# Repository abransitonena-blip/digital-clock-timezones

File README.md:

# AP · Iluminación LED inteligente

Sitio web (React + Vite) y diseños abiertos de electrónica para iluminación LED.

## Secciones del sitio
| Ruta | Qué hace |
|---|---|
| `#` Inicio | Presentación del Cubo AP, líneas de producto y proyectos |
| `#lineas` | 7 líneas de producto con configuración recomendada y ejemplo calculado. Líneas: letreros, arquitectura, hogar, comercio, eventos, solar y vehículos |
| `#cubo` | Ficha del Cubo AP y **panel de control**: Bluetooth (Chrome/Edge) o demo simulada |
| `#configurador` | Pedidos por cliente (V, A, cantidad), con exportación a CSV e impresión. Calcula: cubos, cartucho, tarjeta con R_B/R_ID, cable, lista de compra y **cotización** (tus costos, margen e IVA) |
| `#calculadora` | Consumo, reinyección, cubos y caída en cable para 15 tiras del mercado. Incluye la tarjeta a la medida (R_B E96) |
| `#compatibilidad` | Compatibilidad con tiras, apps, asistentes de voz y fuentes de energía |
| `#instalar` | Graba el firmware del Cubo AP por USB desde Chrome o Edge (ESP Web Tools empaquetado, sin CDN) |
| `#proyectos` | Todos los proyectos de `hardware/`, con manuales, esquemas, Gerber y BOM |
| `#reloj` | El reloj mundial original (zonas horarias, alarmas, temas) |

```
npm install
npm run dev      # http://localhost:3000
npm test         # pruebas de los cálculos (src/lib/led.test.js)
npm run build    # sitio estático en dist/ (rutas relativas: sirve en GitHub Pages o cualquier hosting)
```
- `src/lib/led.js` tiene los cálculos, sin React. Sus perfiles de tarjeta son los mismos del firmware.
- `src/datos/catalogo.js` tiene las tiras, las líneas de producto, la compatibilidad y los proyectos.
- `public/cubo-app.html` es el panel ligero; se copia al compilar desde `hardware/cubo-led-modular/app/index.html`, y es la misma página que el cubo sirve por Wi-Fi.

## Publicar
- **GitHub Pages:** `.github/workflows/pages.yml` compila, prueba y publica en cada push a `main`. Hay que activarlo una vez en *Settings → Pages → Source: GitHub Actions*.
- **Sin internet:** el sitio se puede instalar en el celular o la PC como app (PWA). Después de la primera visita funciona sin red; esto requiere HTTPS o localhost.

Los diseños están sin fabricar ni certificar. Los consumos de tiras son típicos: confírmalos con la ficha del fabricante.

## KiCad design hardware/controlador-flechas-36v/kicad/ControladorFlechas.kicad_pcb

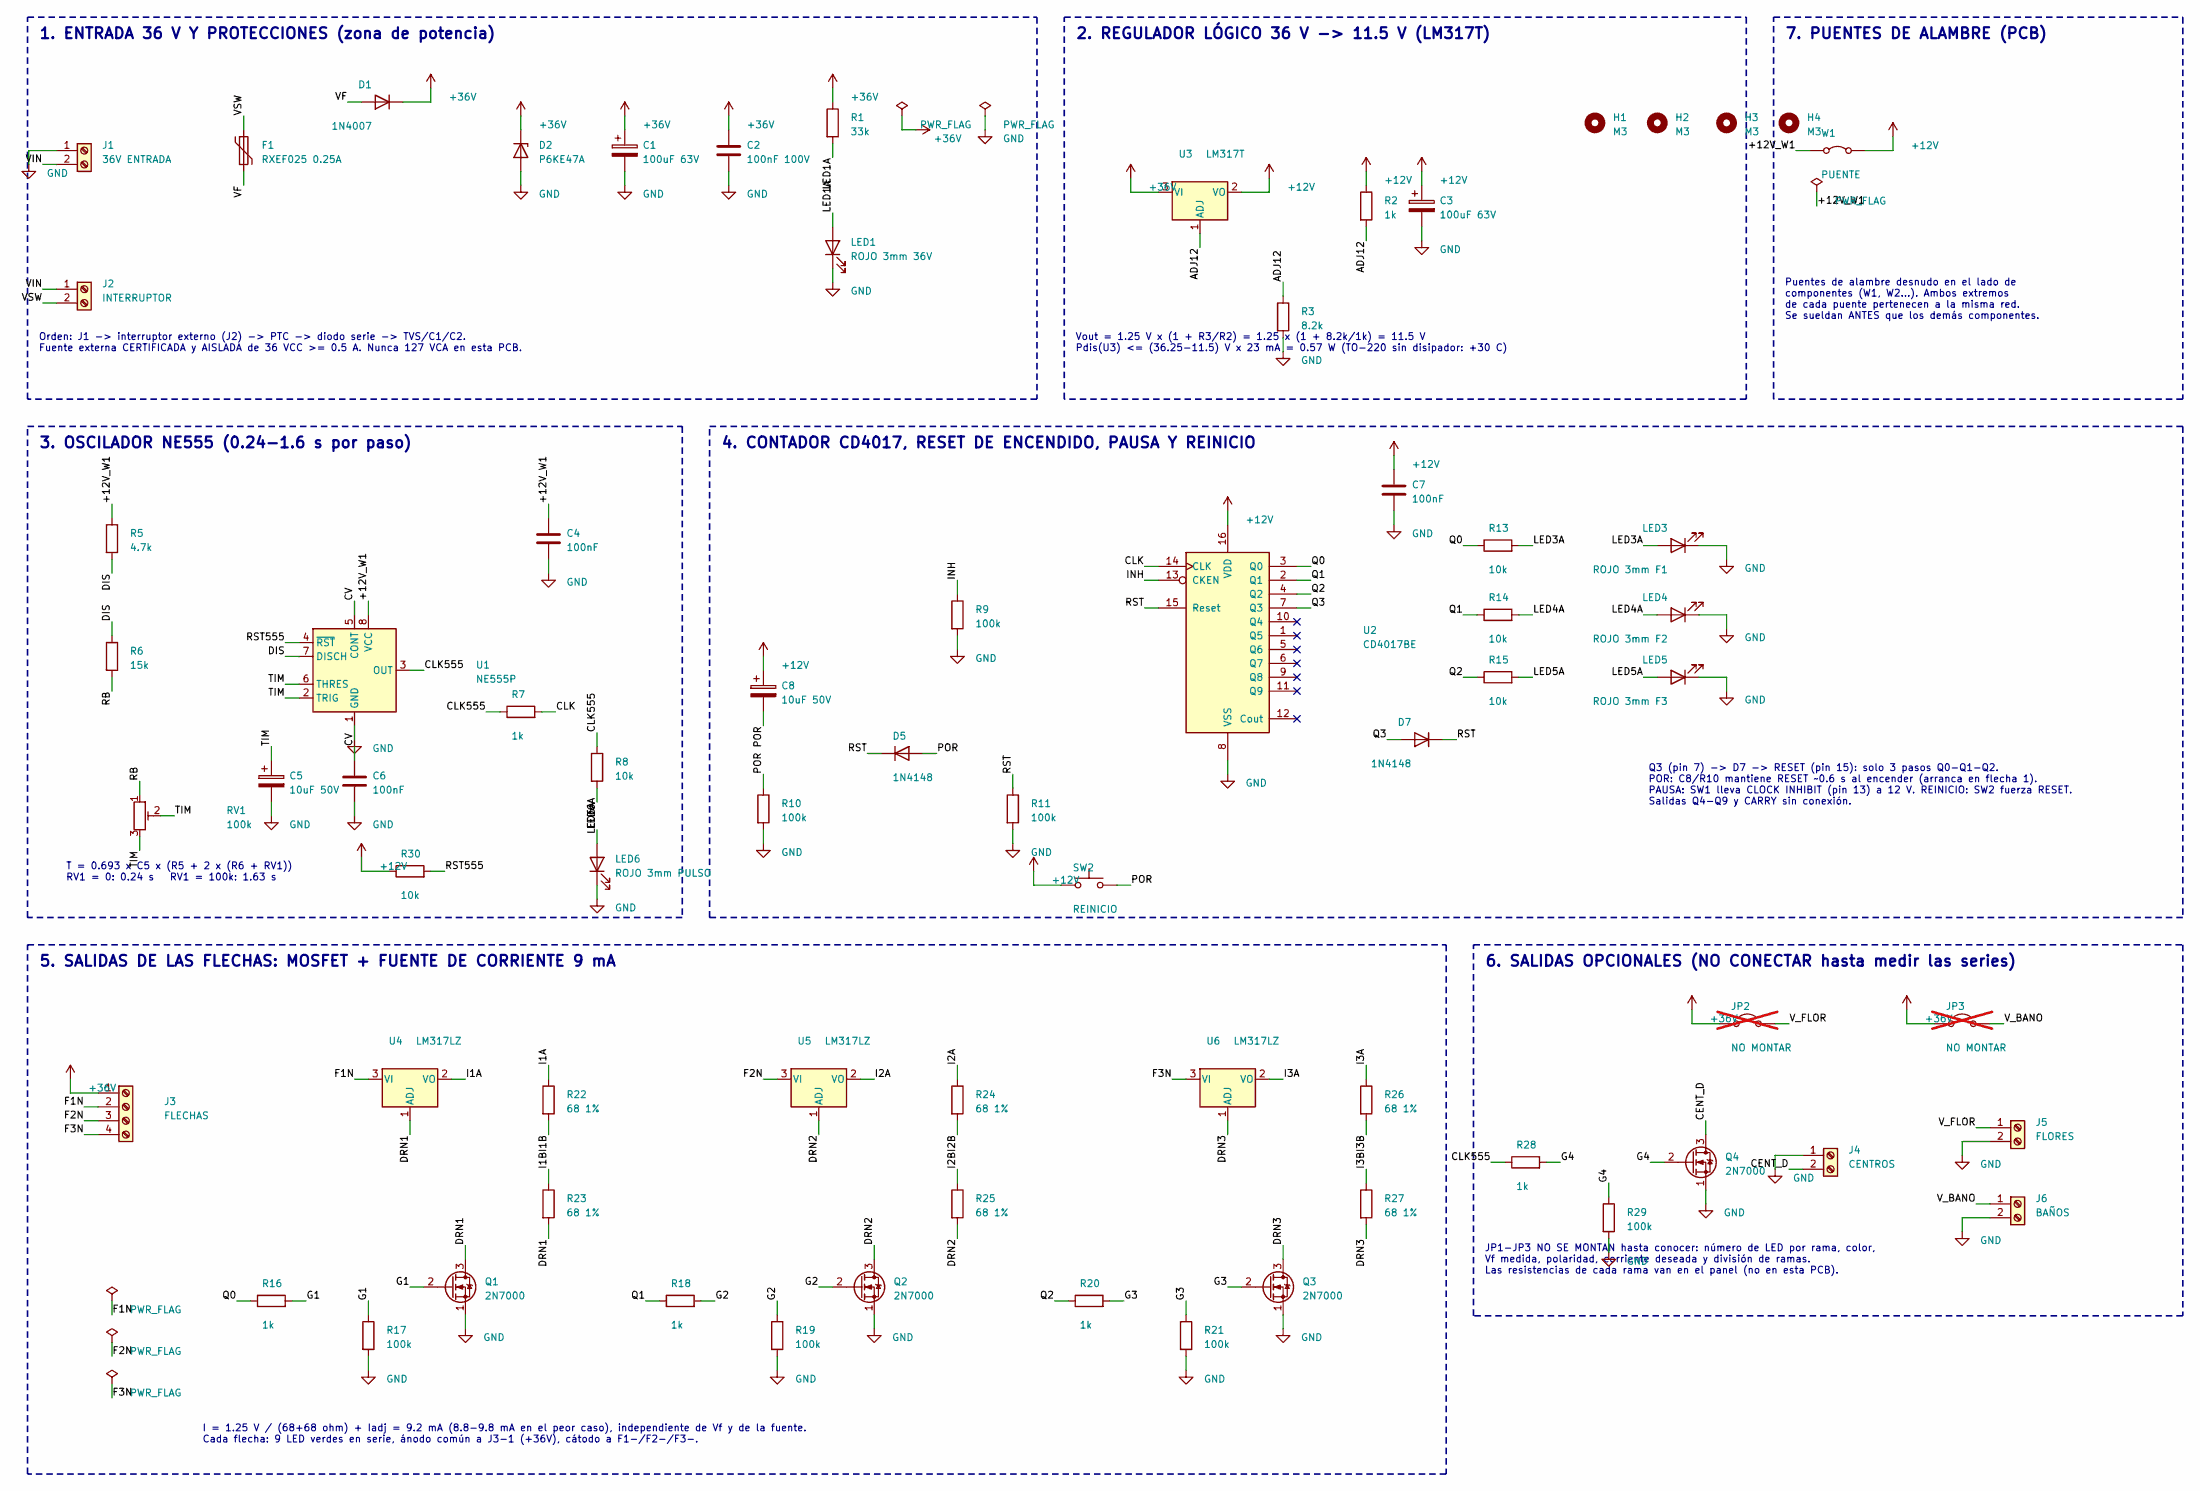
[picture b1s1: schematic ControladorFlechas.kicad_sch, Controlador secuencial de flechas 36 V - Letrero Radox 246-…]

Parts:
C1, C3: 100uF 63V; CP_Radial_D8.0mm_P3.81mm
C2: 100nF 100V; C_Disc_P5.08mm
C4, C6, C7: 100nF; C_Disc_P5.08mm
C5, C8: 10uF 50V; CP_Radial_D5.0mm_P2.54mm
D1: 1N4007; D_DO-41_P10.16mm
D2: P6KE47A; D_DO-15_P12.70mm
D5, D7: 1N4148; D_DO-35_P7.62mm
F1: RXEF025 0.25A; PTC_Radial_P5.08mm
H1, H2, H3, H4: M3; Barreno_M3_3.2mm
J1: 36V ENTRADA; Clema_2P_P5.08mm
J2: INTERRUPTOR; Clema_2P_P5.08mm
J3: FLECHAS; Clema_4P_P5.08mm
J4: CENTROS; Clema_2P_P5.08mm
J5: FLORES; Clema_2P_P5.08mm
J6: BAÑOS; Clema_2P_P5.08mm
JP2, JP3: NO MONTAR; Enlace_Opcional_P7.62mm; not fitted
LED1: ROJO 3mm 36V; LED_D3.0mm
LED3: ROJO 3mm F1; LED_D3.0mm
LED4: ROJO 3mm F2; LED_D3.0mm
LED5: ROJO 3mm F3; LED_D3.0mm
LED6: ROJO 3mm PULSO; LED_D3.0mm
Q1, Q2, Q3, Q4: 2N7000; TO-92_2N7000
R1: 33k; R_Vertical_P5.08mm
R2, R28: 1k; R_Vertical_P5.08mm
R3: 8.2k; R_Vertical_P5.08mm
R5: 4.7k; R_Vertical_P5.08mm
R6: 15k; R_Vertical_P5.08mm
R7, R16, R18, R20: 1k; R_Axial_P10.16mm
R8, R13, R14, R15: 10k; R_Vertical_P5.08mm
R9: 100k; R_Axial_P10.16mm
R10, R11, R17, R19, R21, R29: 100k; R_Vertical_P5.08mm
R22, R23, R24, R25, R26, R27: 68 1%; R_Vertical_P5.08mm
R30: 10k; R_Axial_P10.16mm
RV1: 100k; Trimpot_3296W
SW2: REINICIO; Boton_6mm
U1: NE555P; DIP-8_W7.62mm
U2: CD4017BE; DIP-16_W7.62mm
U3: LM317T; TO-220-3_Vertical
U4, U5, U6: LM317LZ; TO-92_LM317L
W1: PUENTE; Puente_Alambre_P7.62mm

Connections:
+12V: C3.1, C7.1, C8.1, R2.1, R30.1, SW2.1, U2.16 (VDD), U3.2 (VO), W1.2 (B)
+36V: C1.1, C2.1, D1.1 (K), D2.1 (K), J3.1, JP2.1 (A), JP3.1 (A), R1.1, U3.3 (VI)
/+12V_W1: C4.1, R5.1, U1.8 (VCC), W1.1 (A)
/ADJ12: R2.2, R3.1, U3.1 (ADJ)
/CENT_D: J4.2, Q4.3 (D)
/CLK: R7.2, U2.14 (CLK)
/CLK555: R7.1, R8.1, R28.1, U1.3 (OUT)
/CV: C6.1, U1.5 (CONT)
/DIS: R5.2, R6.1, U1.7 (DISCH)
/DRN1: Q1.3 (D), R23.2, U4.1 (ADJ)
/DRN2: Q2.3 (D), R25.2, U5.1 (ADJ)
/DRN3: Q3.3 (D), R27.2, U6.1 (ADJ)
/F1N: J3.2, U4.3 (VI)
/F2N: J3.3, U5.3 (VI)
/F3N: J3.4, U6.3 (VI)
/G1: Q1.2 (G), R16.2, R17.1
/G2: Q2.2 (G), R18.2, R19.1
/G3: Q3.2 (G), R20.2, R21.1
/G4: Q4.2 (G), R28.2, R29.1
/I1A: R22.1, U4.2 (VO)
/I1B: R22.2, R23.1
/I2A: R24.1, U5.2 (VO)
/I2B: R24.2, R25.1
/I3A: R26.1, U6.2 (VO)
/I3B: R26.2, R27.1
/INH: R9.1, U2.13 (CKEN)
/LED1A: LED1.2 (A), R1.2
/LED3A: LED3.2 (A), R13.2
/LED4A: LED4.2 (A), R14.2
/LED5A: LED5.2 (A), R15.2
/LED6A: LED6.2 (A), R8.2
/POR: C8.2, D5.2 (A), R10.1, SW2.2
/Q0: R13.1, R16.1, U2.3 (Q0)
/Q1: R14.1, R18.1, U2.2 (Q1)
/Q2: R15.1, R20.1, U2.4 (Q2)
/Q3: D7.2 (A), U2.7 (Q3)
/RB: R6.2, RV1.1
/RST: D5.1 (K), D7.1 (K), R11.1, U2.15 (Reset)
/RST555: R30.2, U1.4 (~RST)
/TIM: C5.1, RV1.2, RV1.3, U1.2 (TRIG), U1.6 (THRES)
/VF: D1.2 (A), F1.2
/VIN: J1.2, J2.1
/VSW: F1.1, J2.2
/V_BANO: J6.1, JP3.2 (B)
/V_FLOR: J5.1, JP2.2 (B)
GND: C1.2, C2.2, C3.2, C4.2, C5.2, C6.2, C7.2, D2.2 (A), J1.1, J4.1, J5.2, J6.2, LED1.1 (K), LED3.1 (K), LED4.1 (K), LED5.1 (K), LED6.1 (K), Q1.1 (S), Q2.1 (S), Q3.1 (S), Q4.1 (S), R3.2, R9.2, R10.2, R11.2, R17.2, R19.2, R21.2, R29.2, U1.1 (GND), U2.8 (VSS)

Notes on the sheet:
1. ENTRADA 36 V Y PROTECCIONES (zona de potencia)
2. REGULADOR LÓGICO 36 V -> 11.5 V (LM317T)
3. OSCILADOR NE555 (0.24-1.6 s por paso)
4. CONTADOR CD4017, RESET DE ENCENDIDO, PAUSA Y REINICIO
5. SALIDAS DE LAS FLECHAS: MOSFET + FUENTE DE CORRIENTE 9 mA
6. SALIDAS OPCIONALES (NO CONECTAR hasta medir las series)
7. PUENTES DE ALAMBRE (PCB)
Orden: J1 -> interruptor externo (J2) -> PTC -> diodo serie -> TVS/C1/C2. Fuente externa CERTIFICADA y AISLADA de 36 VCC >= 0.5 A. Nunca 127 VCA en esta PCB.
Vout = 1.25 V x (1 + R3/R2) = 1.25 x (1 + 8.2k/1k) = 11.5 V Pdis(U3) <= (36.25-11.5) V x 23 mA = 0.57 W (TO-220 sin disipador: +30 C)
T = 0.693 x C5 x (R5 + 2 x (R6 + RV1)) RV1 = 0: 0.24 s RV1 = 100k: 1.63 s
Q3 (pin 7) -> D7 -> RESET (pin 15): solo 3 pasos Q0-Q1-Q2. POR: C8/R10 mantiene RESET ~0.6 s al encender (arranca en flecha 1). PAUSA: SW1 lleva CLOCK INHIBIT (pin 13) a 12 V. REINICIO: SW2 fuerza RESET. Salidas Q4-Q9 y CARRY sin conexión.
I = 1.25 V / (68+68 ohm) + Iadj = 9.2 mA (8.8-9.8 mA en el peor caso), independiente de Vf y de la fuente. Cada flecha: 9 LED verdes en serie, ánodo común a J3-1 (+36V), cátodo a F1-/F2-/F3-.
Puentes de alambre desnudo en el lado de componentes (W1, W2...). Ambos extremos de cada puente pertenecen a la misma red. Se sueldan ANTES que los demás componentes.
JP1-JP3 NO SE MONTAN hasta conocer: número de LED por rama, color, Vf medida, polaridad, corriente deseada y división de ramas. Las resistencias de cada rama van en el panel (no en esta PCB).

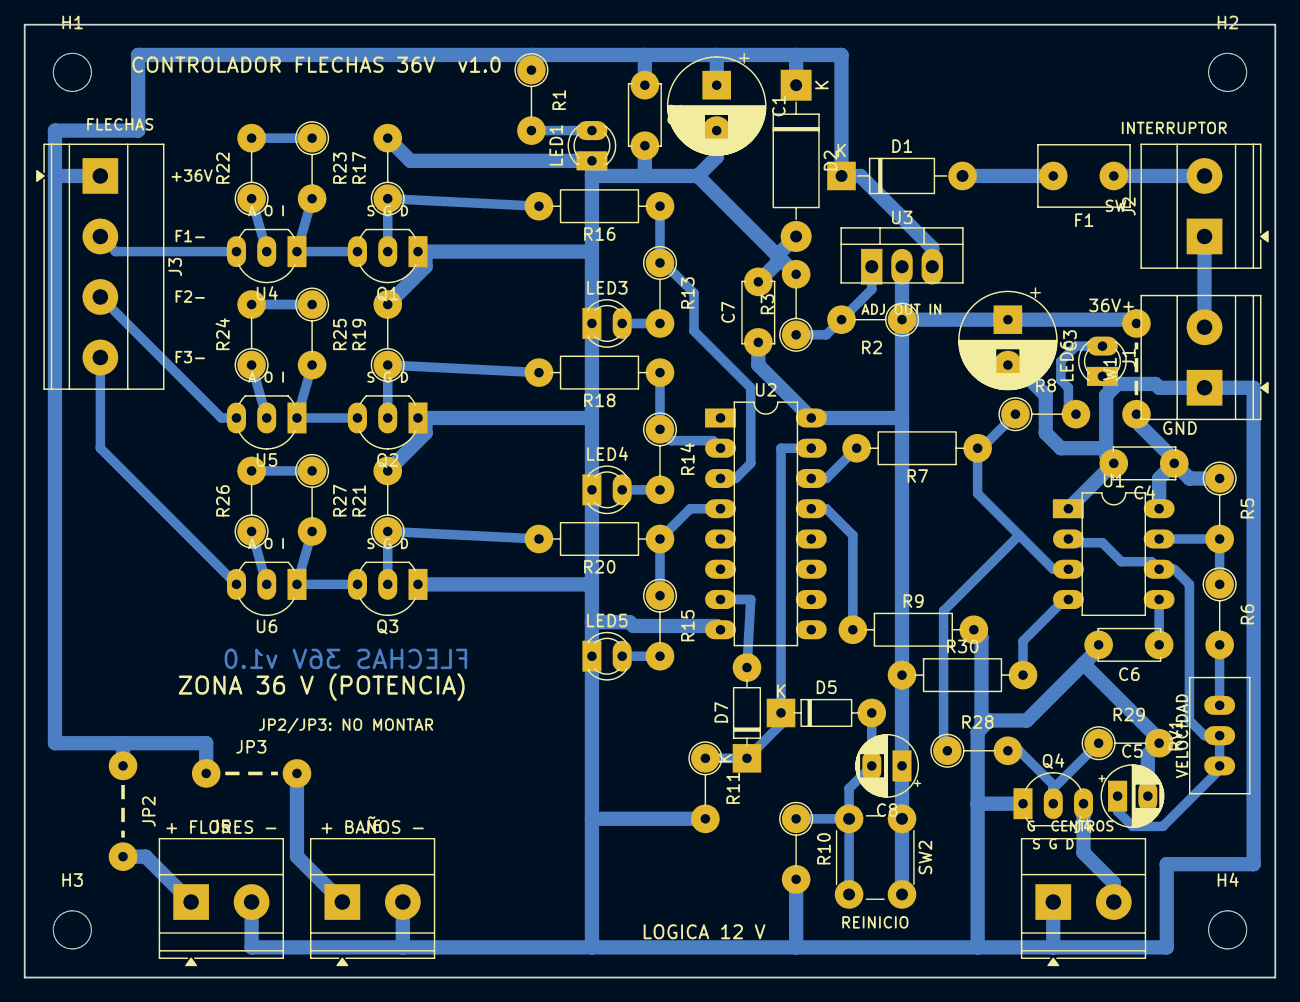
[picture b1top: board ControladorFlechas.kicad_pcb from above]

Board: 2 copper layers, 105.0 x 80.0 mm, 71 parts (0 on the bottom side), 46 nets.

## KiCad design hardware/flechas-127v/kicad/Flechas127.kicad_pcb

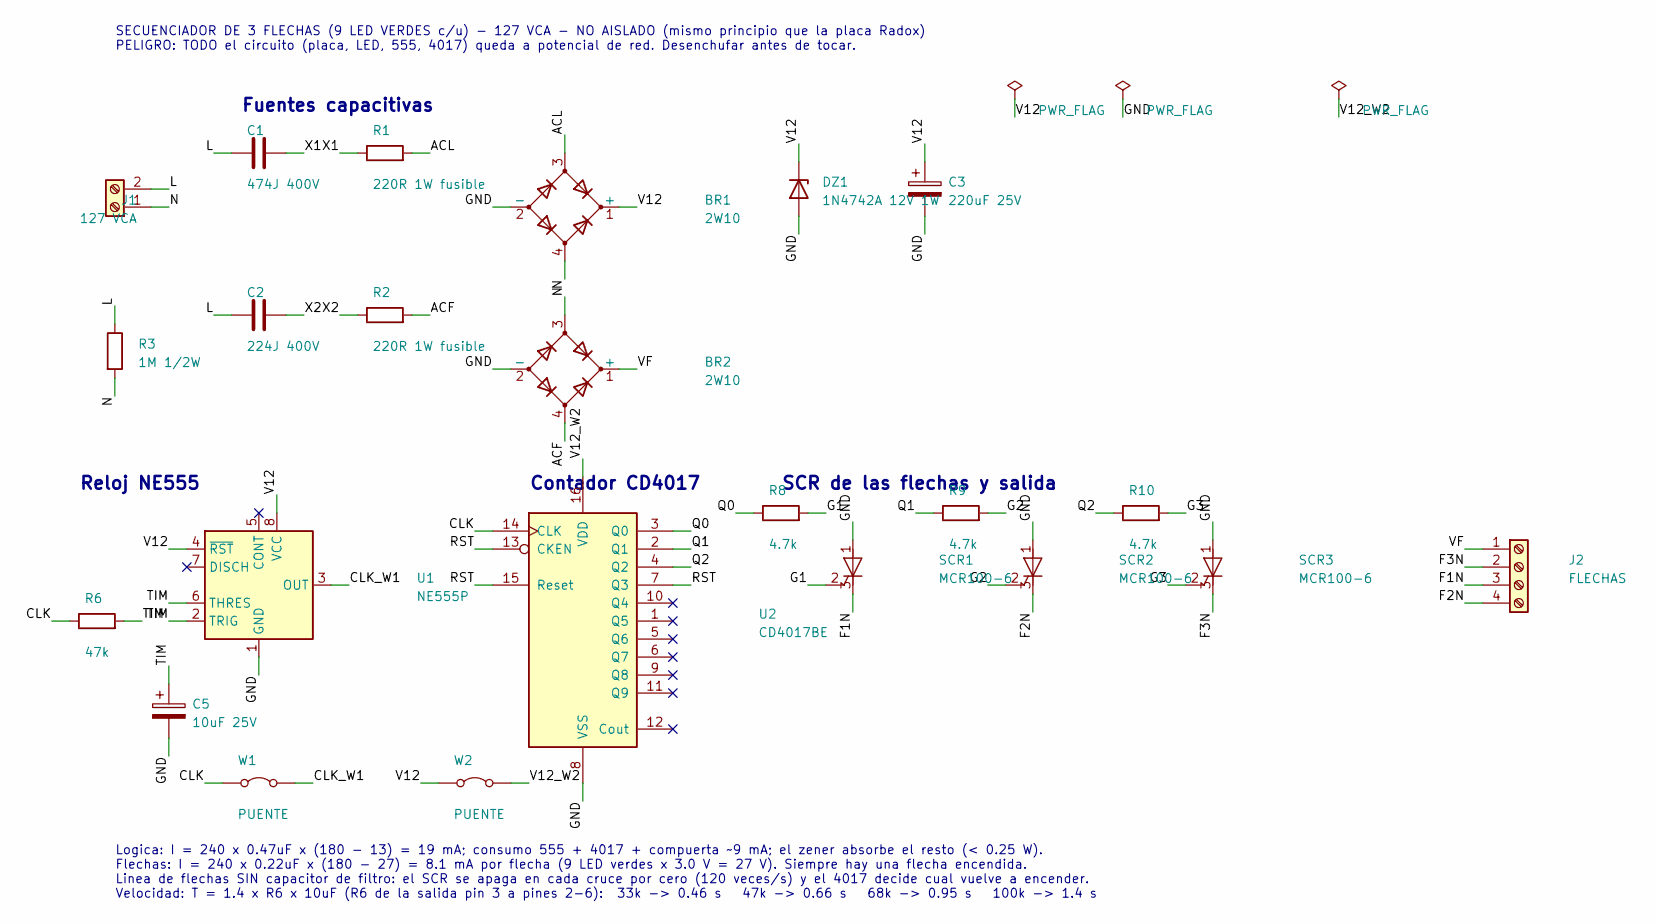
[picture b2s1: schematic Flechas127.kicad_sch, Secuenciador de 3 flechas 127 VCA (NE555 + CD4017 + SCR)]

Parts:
BR1, BR2: 2W10; Puente_2W10
C1: 474J 400V; C_Poliester_P10-15mm
C2: 224J 400V; C_Poliester_P10-15mm
C3: 220uF 25V; CP_Radial_D8.0mm_P3.81mm
C5: 10uF 25V; CP_Radial_D5.0mm_P2.54mm
DZ1: 1N4742A 12V 1W; D_DO-41_P10.16mm
J1: 127 VCA; Clema_2P_P5.08mm
J2: FLECHAS; Cables_4P_P5.08mm
R1, R2: 220R 1W fusible; R_1W_Vertical_P7.62mm
R3: 1M 1/2W; R_Vertical_P5.08mm
R6: 47k; R_Vertical_P5.08mm
R8, R9, R10: 4.7k; R_Vertical_P5.08mm
SCR1, SCR2, SCR3: MCR100-6; TO-92_SCR
U1: NE555P; DIP-8_W7.62mm
U2: CD4017BE; DIP-16_W7.62mm
W1: PUENTE; Puente_Abajo_P7.62mm
W2: PUENTE; Puente_Abajo_P10.16mm

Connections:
/ACF: BR2.4, R2.2
/ACL: BR1.3, R1.2
/CLK: R6.1, U2.14 (CLK), W1.1 (A)
/CLK_W1: U1.3 (OUT), W1.2 (B)
/F1N: J2.3, SCR1.3 (K)
/F2N: J2.4, SCR2.3 (K)
/F3N: J2.2, SCR3.3 (K)
/G1: R8.2, SCR1.2 (G)
/G2: R9.2, SCR2.2 (G)
/G3: R10.2, SCR3.2 (G)
/GND: BR1.2 (-), BR2.2 (-), C3.2, C5.2, DZ1.2 (A), SCR1.1 (A), SCR2.1 (A), SCR3.1 (A), U1.1 (GND), U2.8 (VSS)
/L: C1.1, C2.1, J1.2, R3.1
/N: BR1.4, BR2.3, J1.1, R3.2
/Q0: R8.1, U2.3 (Q0)
/Q1: R9.1, U2.2 (Q1)
/Q2: R10.1, U2.4 (Q2)
/RST: U2.7 (Q3), U2.13 (CKEN), U2.15 (Reset)
/TIM: C5.1, R6.2, U1.2 (TRIG), U1.6 (THRES)
/V12: BR1.1 (+), C3.1, DZ1.1 (K), U1.4 (~RST), U1.8 (VCC), W2.1 (A)
/V12_W2: U2.16 (VDD), W2.2 (B)
/VF: BR2.1 (+), J2.1
/X1: C1.2, R1.1
/X2: C2.2, R2.1

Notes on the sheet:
SECUENCIADOR DE 3 FLECHAS (9 LED VERDES c/u) - 127 VCA - NO AISLADO (mismo principio que la placa Radox) PELIGRO: TODO el circuito (placa, LED, 555, 4017) queda a potencial de red. Desenchufar antes de tocar.
Logica: I = 240 x 0.47uF x (180 - 13) = 19 mA; consumo 555 + 4017 + compuerta ~9 mA; el zener absorbe el resto (< 0.25 W). Flechas: I = 240 x 0.22uF x (180 - 27) = 8.1 mA por flecha (9 LED verdes x 3.0 V = 27 V). Siempre hay una flecha encendida. Linea de flechas SIN capacitor de filtro: el SCR se 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
Fuentes capacitivas
Reloj NE555
Contador CD4017
SCR de las flechas y salida

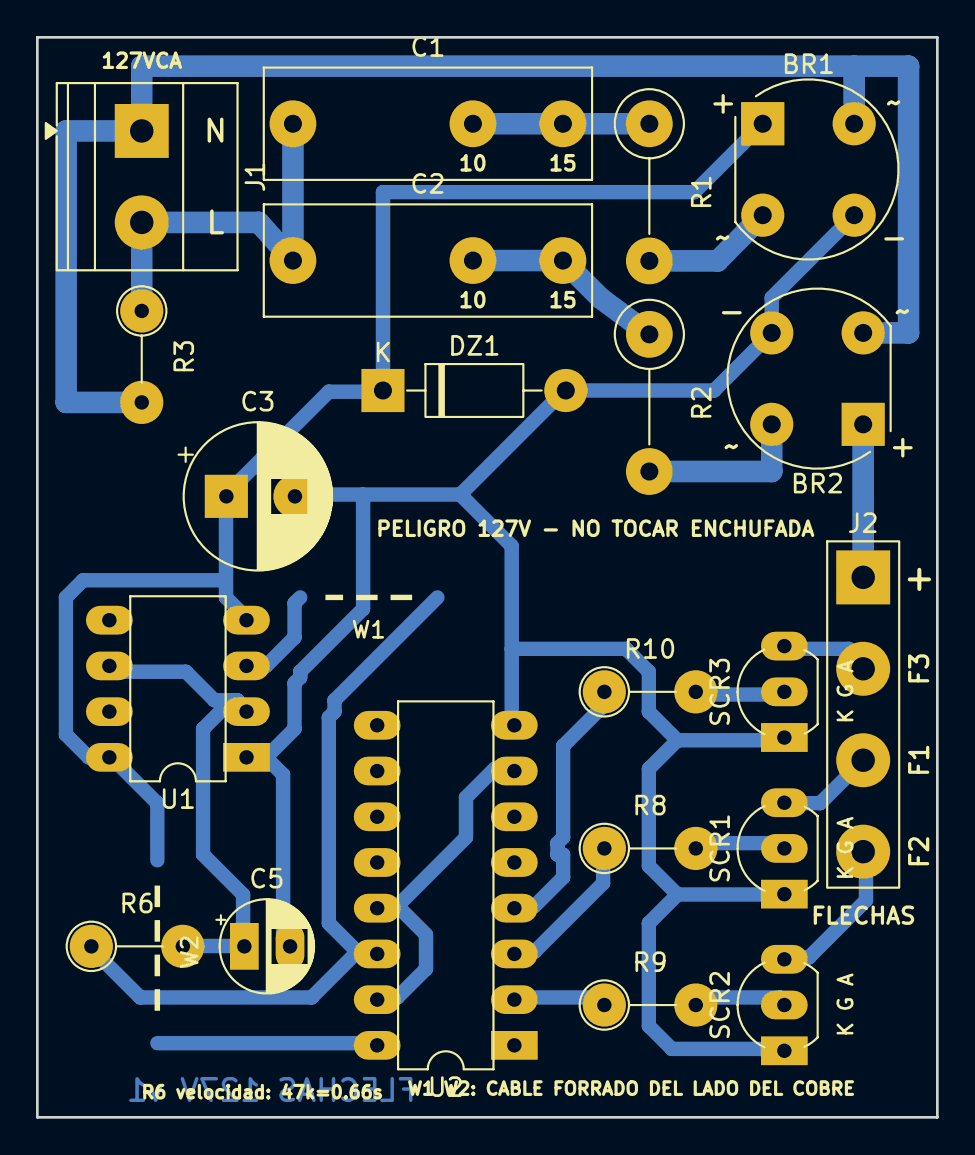
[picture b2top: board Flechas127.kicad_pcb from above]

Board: 2 copper layers, 50.0 x 60.0 mm, 23 parts (0 on the bottom side), 23 nets.

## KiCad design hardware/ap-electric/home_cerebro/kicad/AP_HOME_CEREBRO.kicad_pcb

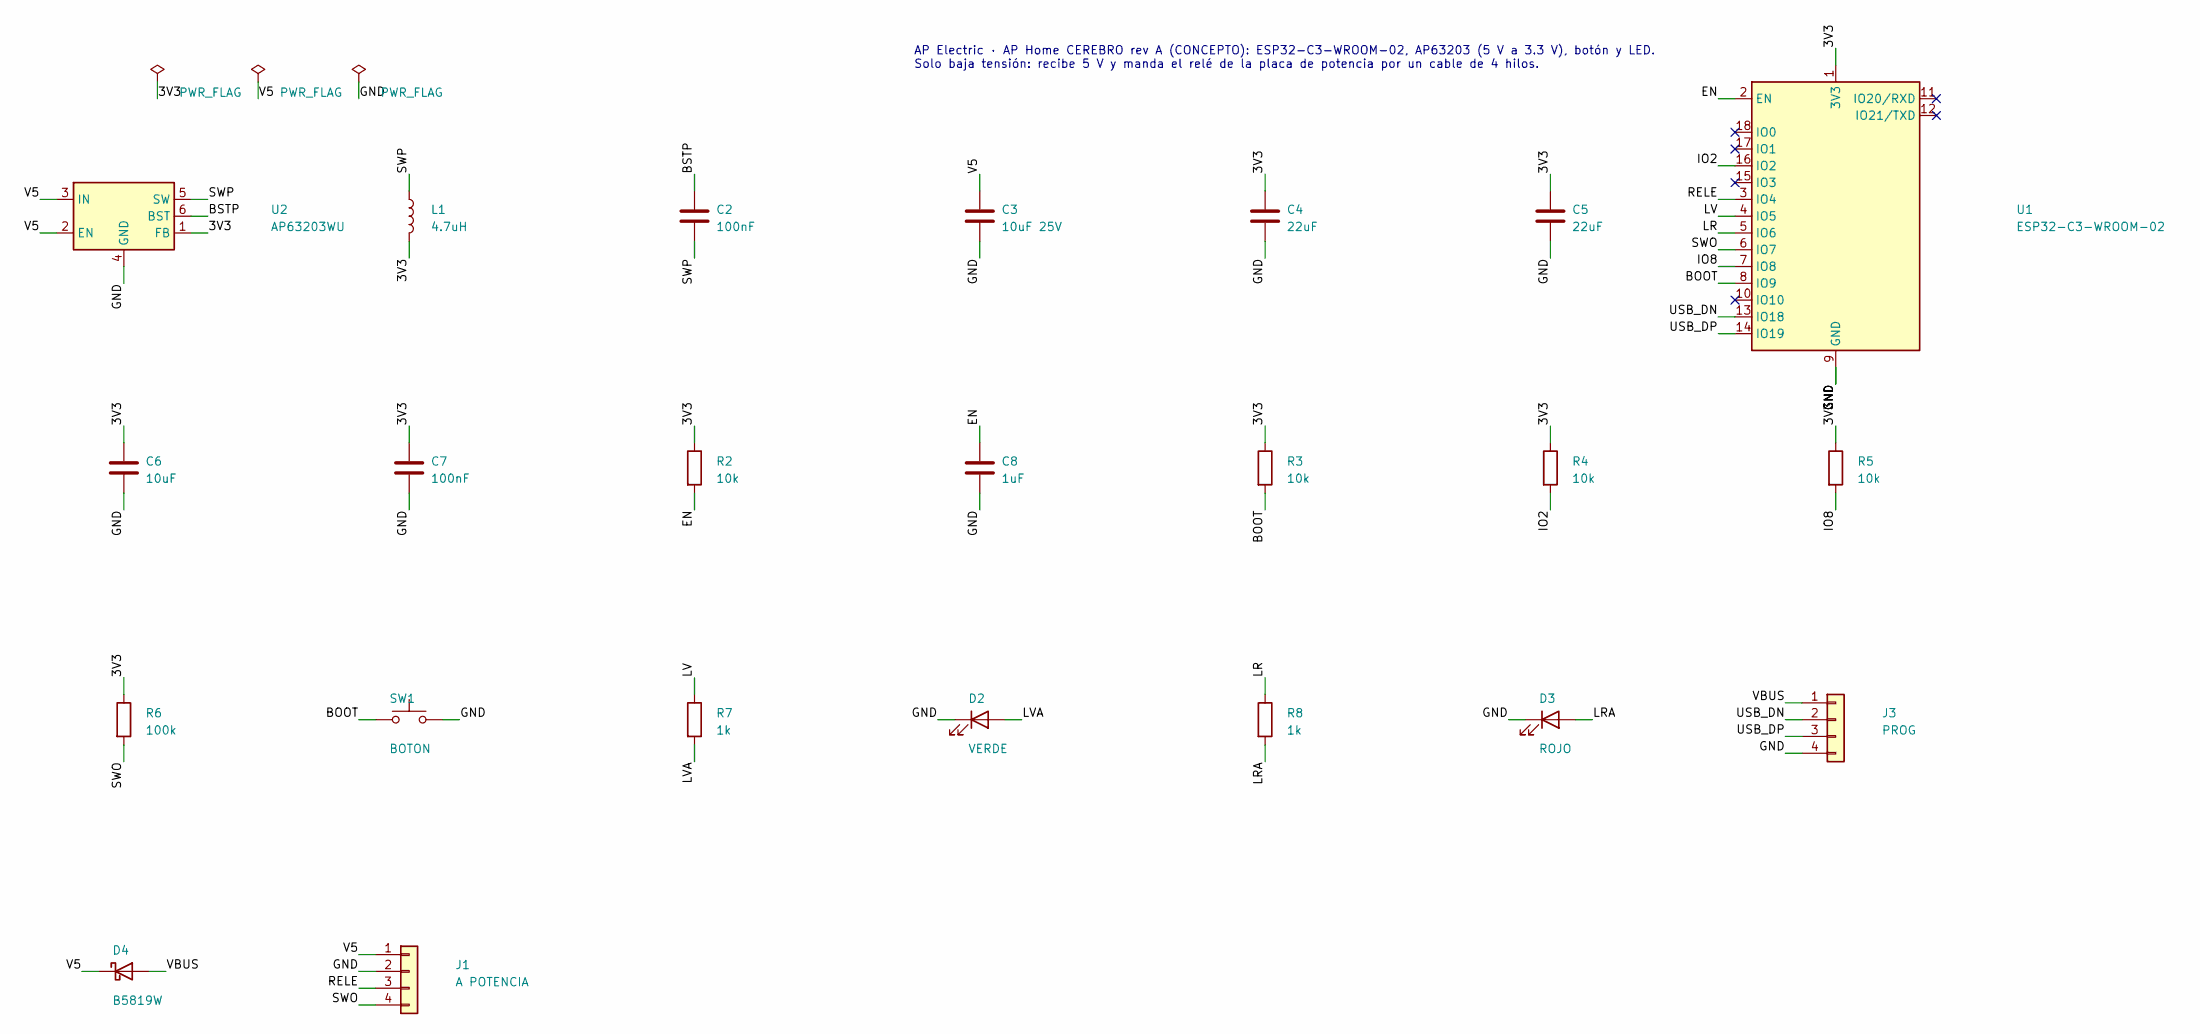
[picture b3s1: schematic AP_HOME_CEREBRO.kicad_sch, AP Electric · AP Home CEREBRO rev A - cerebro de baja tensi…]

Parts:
C2, C7: 100nF; C_0603_1608Metric
C3: 10uF 25V; C_1206_3216Metric
C4, C5: 22uF; C_0805_2012Metric
C6: 10uF; C_0805_2012Metric
C8: 1uF; C_0603_1608Metric
D2: VERDE; LED_0603_1608Metric
D3: ROJO; LED_0603_1608Metric
D4: B5819W; D_SOD-123
J1: A POTENCIA; JST_XH_B4B-XH-A_1x04_P2.50mm_Vertical
J3: PROG; PinHeader_1x04_P2.54mm_Vertical
L1: 4.7uH; L_Changjiang_FNR4030S
R2, R3, R4, R5: 10k; R_0603_1608Metric
R6: 100k; R_0603_1608Metric
R7, R8: 1k; R_0603_1608Metric
SW1: BOTON; SW_Push_1P1T_XKB_TS-1187A
U1: ESP32-C3-WROOM-02; ESP32-C3-WROOM-02_JLC
U2: AP63203WU; TSOT-23-6

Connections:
/3V3: C4.1, C5.1, C6.1, C7.1, L1.2, R2.1, R3.1, R4.1, R5.1, R6.1, U1.1 (3V3), U2.1 (FB)
/BOOT: R3.2, SW1.1, U1.8 (IO9)
/BSTP: C2.1, U2.6 (BST)
/EN: C8.1, R2.2, U1.2 (EN)
/GND: C3.2, C4.2, C5.2, C6.2, C7.2, C8.2, D2.1 (K), D3.1 (K), J1.2, J3.4, SW1.2, U1.9 (GND), U1.19 (GND), U2.4 (GND)
/IO2: R4.2, U1.16 (IO2)
/IO8: R5.2, U1.7 (IO8)
/LR: R8.1, U1.5 (IO6)
/LRA: D3.2 (A), R8.2
/LV: R7.1, U1.4 (IO5)
/LVA: D2.2 (A), R7.2
/RELE: J1.3, U1.3 (IO4)
/SWO: J1.4, R6.2, U1.6 (IO7)
/SWP: C2.2, L1.1, U2.5 (SW)
/USB_DN: J3.2, U1.13 (IO18)
/USB_DP: J3.3, U1.14 (IO19)
/V5: C3.1, D4.1 (K), J1.1, U2.2 (EN), U2.3 (IN)
/VBUS: D4.2 (A), J3.1

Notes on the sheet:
AP Electric · AP Home CEREBRO rev A (CONCEPTO): ESP32-C3-WROOM-02, AP63203 (5 V a 3.3 V), botón y LED. Solo baja tensión: recibe 5 V y manda el relé de la placa de potencia por un cable de 4 hilos.

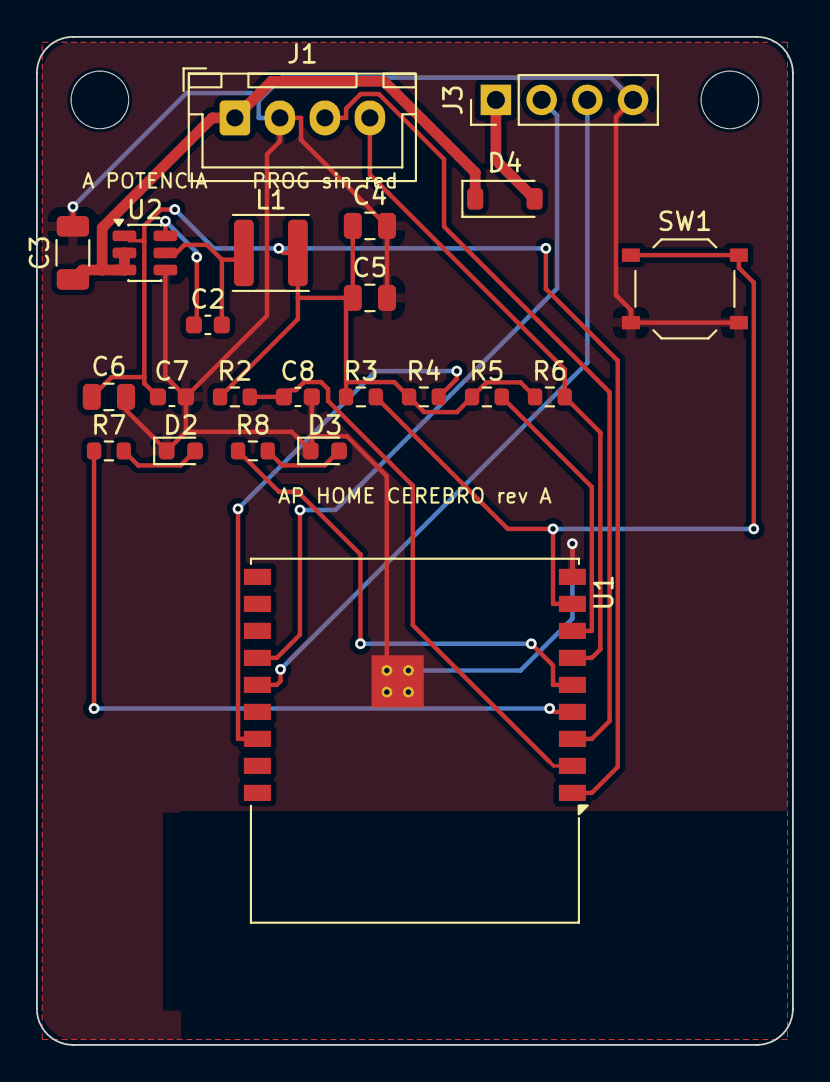
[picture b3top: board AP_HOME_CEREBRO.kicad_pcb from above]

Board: 2 copper layers, 42.0 x 56.0 mm, 25 parts (0 on the bottom side), 18 nets.

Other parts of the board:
H1, H2: MountingHole_3.2mm_M3

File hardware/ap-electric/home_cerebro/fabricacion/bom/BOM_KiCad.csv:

"Referencia","Valor","Huella","Cantidad","Funcion"
"C2,C7","100nF","Capacitor_SMD:C_0603_1608Metric","2","Bootstrap,Desacoplo del módulo"
"C3","10uF 25V","Capacitor_SMD:C_1206_3216Metric","1","Entrada del buck"
"C4,C5","22uF","Capacitor_SMD:C_0805_2012Metric","2","Salida 3.3 V"
"C6","10uF","Capacitor_SMD:C_0805_2012Metric","1","Desacoplo del módulo"
"C8","1uF","Capacitor_SMD:C_0603_1608Metric","1","Arranque retardado"
"D2","VERDE","LED_SMD:LED_0603_1608Metric","1","Encendido"
"D3","ROJO","LED_SMD:LED_0603_1608Metric","1","Falla"
"D4","B5819W","Diode_SMD:D_SOD-123","1","5 V del USB al programar"
"J1","A POTENCIA","Connector_JST:JST_XH_B4B-XH-A_1x04_P2.50mm_Vertical","1","Cable de BAJA tensión a la placa de potencia (JST XH, 1 a 1): 1 = 5 V, 2 = 0 V, 3 = mando del relé (3.3 V), 4 = estado del apagador"
"J3","PROG","Connector_PinHeader_2.54mm:PinHeader_1x04_P2.54mm_Vertical","1","Programación por USB en fábrica, SIN red conectada"
"L1","4.7uH","Inductor_SMD:L_Changjiang_FNR4030S","1","Bobina 3.3 V"
"R2,R3,R4,R5","10k","Resistor_SMD:R_0603_1608Metric","4","IO2 en alto al arrancar,IO8 en alto al arrancar,Pull-up EN,Pull-up IO9"
"R6","100k","Resistor_SMD:R_0603_1608Metric","1","Pull-up de la entrada de apagador"
"R7,R8","1k","Resistor_SMD:R_0603_1608Metric","2","LED rojo,LED verde"
"SW1","BOTON","Button_Switch_SMD:SW_Push_1P1T_XKB_TS-1187A","1","Botón: corto = encender/apagar; 3 s = red de configuración; 10 s = fábrica"
"U1","ESP32-C3-WROOM-02","LetreroLab:ESP32-C3-WROOM-02_JLC","1","IO4 = relé, IO5/IO6 = LED, IO7 = entrada de apagador, IO9 = botón"
"U2","AP63203WU","Package_TO_SOT_SMD:TSOT-23-6","1","Buck 3.3 V"

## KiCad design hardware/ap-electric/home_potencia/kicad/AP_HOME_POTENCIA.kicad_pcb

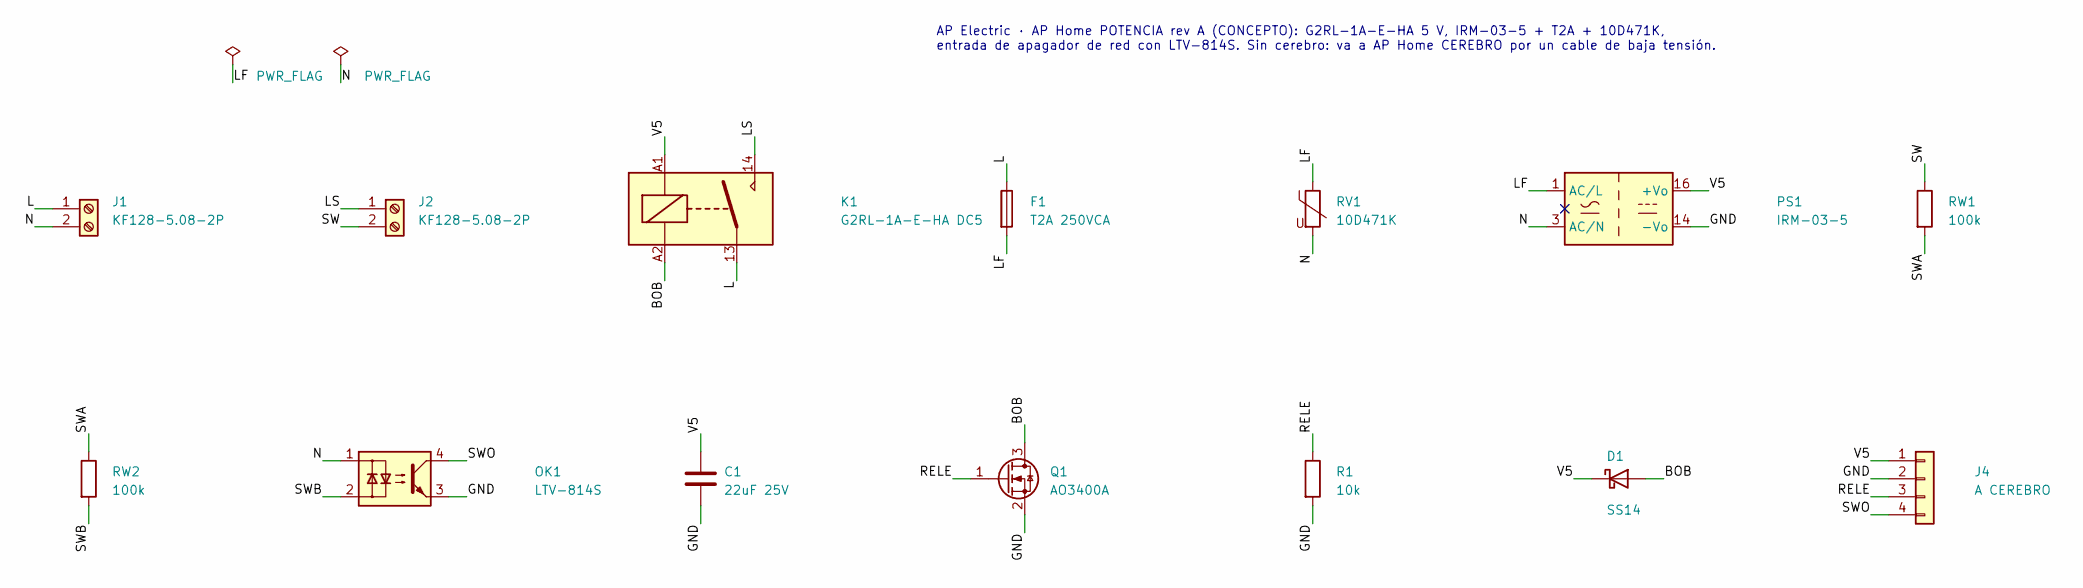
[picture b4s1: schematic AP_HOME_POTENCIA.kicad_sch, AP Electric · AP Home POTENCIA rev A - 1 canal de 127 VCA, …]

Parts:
C1: 22uF 25V; C_1206_3216Metric
D1: SS14; D_SMA
F1: T2A 250VCA; Fuse_2410_6125Metric
J1, J2: KF128-5.08-2P; TerminalBlock_Phoenix_MKDS-1,5-2-5.08_1x02_P5.08mm_Horizont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
J4: A CEREBRO; JST_XH_B4B-XH-A_1x04_P2.50mm_Vertical
K1: G2RL-1A-E-HA DC5; Relay_SPST_Omron_G2RL-1A-E
OK1: LTV-814S; SMDIP-4_W9.53mm
PS1: IRM-03-5; Converter_ACDC_MeanWell_IRM-03-xx_THT
Q1: AO3400A; SOT-23
R1: 10k; R_0603_1608Metric
RV1: 10D471K; RV_Disc_D12mm_W5mm_P7.5mm
RW1, RW2: 100k; R_1206_3216Metric

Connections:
/BOB: D1.2 (A), K1.A2, Q1.3 (D)
/GND: C1.2, J4.2, OK1.3, PS1.14 (-Vo), Q1.2 (S), R1.2
/L: F1.1, J1.1, K1.13
/LF: F1.2, PS1.1 (AC/L), RV1.1
/LS: J2.1, K1.14
/N: J1.2, OK1.1, PS1.3 (AC/N), RV1.2
/RELE: J4.3, Q1.1 (G), R1.1
/SW: J2.2, RW1.1
/SWA: RW1.2, RW2.1
/SWB: OK1.2, RW2.2
/SWO: J4.4, OK1.4
/V5: C1.1, D1.1 (K), J4.1, K1.A1, PS1.16 (+Vo)

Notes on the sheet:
AP Electric · AP Home POTENCIA rev A (CONCEPTO): G2RL-1A-E-HA 5 V, IRM-03-5 + T2A + 10D471K, entrada de apagador de red con LTV-814S. Sin cerebro: va a AP Home CEREBRO por un cable de baja tensión.

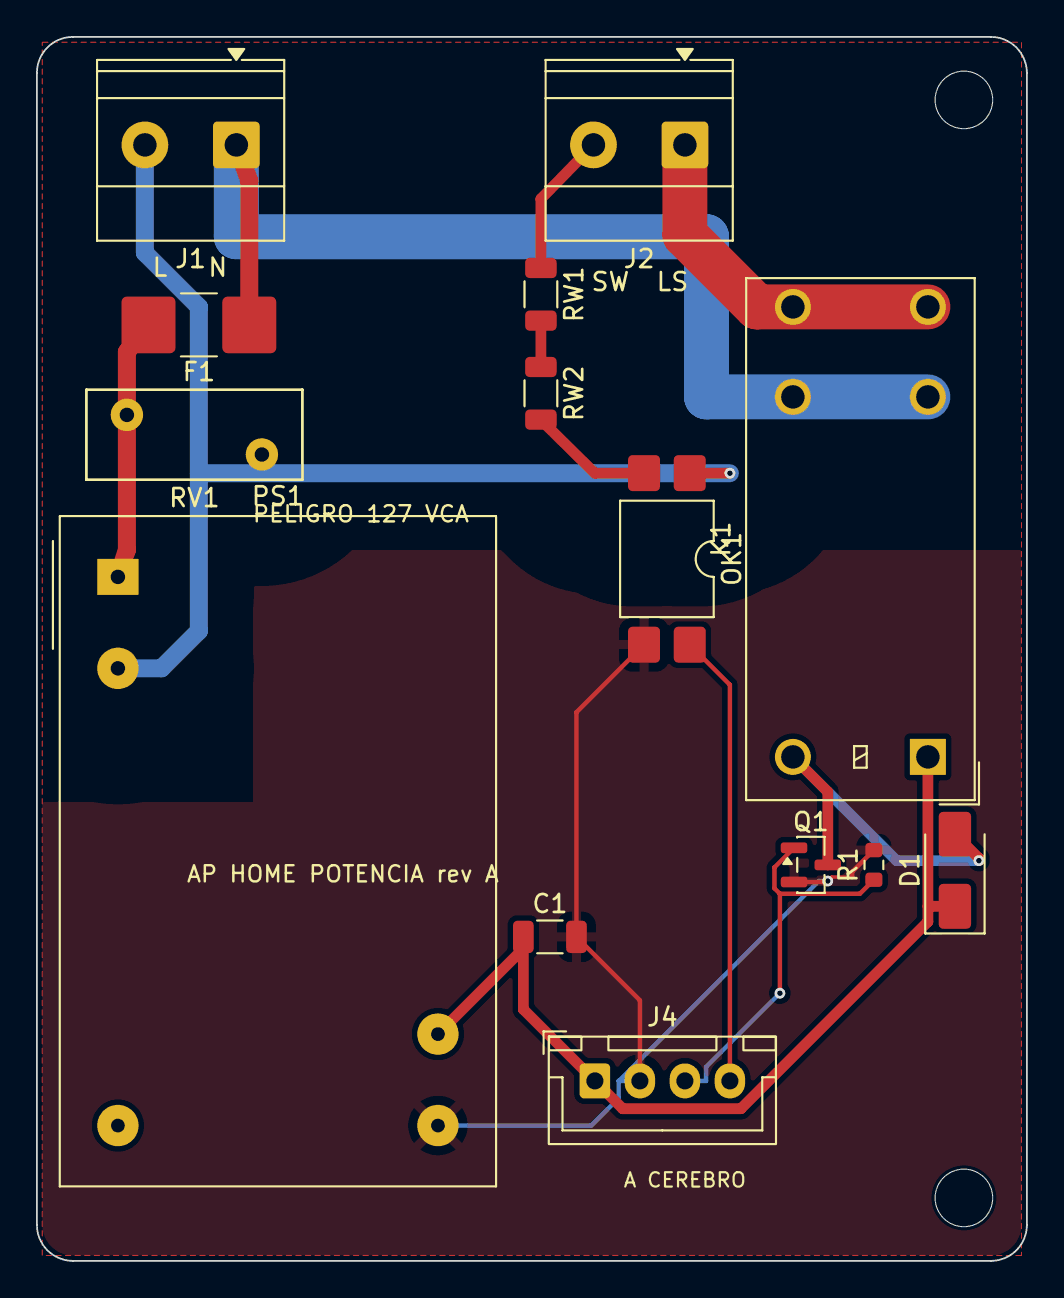
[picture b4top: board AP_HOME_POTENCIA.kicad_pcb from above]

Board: 2 copper layers, 55.0 x 68.0 mm, 16 parts (0 on the bottom side), 12 nets.

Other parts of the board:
H1, H2: MountingHole_3.2mm_M3

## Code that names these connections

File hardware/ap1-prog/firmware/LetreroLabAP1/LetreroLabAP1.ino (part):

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  Protocolo (una línea por orden; también por /api?c=... y MQTT):
     M n  modo 0..9         V n  velocidad 0..9      B n  brillo 0..100     C r g b w  color 0..255
     N n  canales 1..4      P 0|1 todo apagado/encendido                   X 0|1 salida AUX (relevador/contactor)
     O a b  focos de corriente constante 1 y 2: 0..100 %                   Y 0|1 AUX manual / ventilador por temperatura
     E 0|1 ahorro (máx 60%) L 0|1 [lux] solo de noche (sensor de luz Qwiic) S n / R n  guardar/cargar escena 0..3
     H hh:mm hh:mm  ventana diaria encendido   H -  sin ventana
     A i dias hh:mm acc val  horario i=0..7, dias=suma(1=dom,2=lun,4=mar..64=sab; 127=todos),
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uint8_t paso = 0;
bool porHorario = true, porLuz = true;
uint16_t GAMMA12[256];
uint16_t factor = 0;                       // 0..1000: arranque suave x reducción por temperatura
uint32_t dutyActual[4] = {9999, 9999, 9999, 9999};

// mediciones y protección
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// Módulos 0-3 = locales; 4-15 = de los nodos remotos del AP BUS (nodo id: módulos 4 id .. 4 id + 3).
// Salidas S1..S128 (0x20 = S1-S8, 0x21 = S9-S16...), entradas E1..E128 (0x24 = E1-E8...). Al arrancar todo apagado.
const uint8_t IO_LOC = 4, IO_N = IO_LOC * (1 + BUS_NODOS), ACC_NADA = 255;
uint16_t ioOut = 0, ioIn = 0;               // módulos presentes (un bit por módulo)
uint8_t salEstado[IO_N] = {0}, entEstado[IO_N] = {0}, entCrudo[IO_N] = {0};
struct Regla { uint8_t acc, val, modo; };   // qué hace cada entrada al activarse (modo 1: al soltar, lo contrario)
Regla reglas[IO_N * 8];
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uint32_t busRx = 0, busTx = 0;
uint8_t busEnLinea();                       // (más abajo, junto al AP BUS)
// ---- AP GATE: maestro Modbus RTU por RS-485 (IO6 = TX, IO7 = RX, IO1 = DE y /RE) ----
uint8_t PIN_RS_TX = 6, PIN_RS_RX = 7, PIN_RS_DE = 1;     // AP GATE; en el AP UNO: IO1/IO3 y DE en el expansor (255)
const uint8_t MB_N = 8;
uint32_t mbBaud = 0;                        // 0 = apagado
uint8_t mbParidad = 0;
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const uint8_t ACC_MAX = 11;
uint16_t luMods = 0;                        // bit m = módulo LU_DIR[m] presente
uint8_t luNivel[LU_N];                      // 0-100: el último nivel pedido
uint64_t luOn = 0, luSigue = 0;             // encendida / sigue a la luz principal (un bit por luminaria)
// ---- AP FOCO: corriente medida (INA238 0x4C + f) y máxima según la resistencia de ID del foco ----
const uint8_t FC_N = 4, FC_INA = 0x4C;
enum { FC_NO = 0, FC_BIEN, FC_ABIERTO, FC_ID_CORTO, FC_SOBRE, FC_SIN_ID, FC_CORTA };
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  }
  return true;
}
void eepEscribir(uint8_t dir, const void* buf, uint8_t n) {   // páginas de 8 bytes; 5 ms por página
  const uint8_t* b = (const uint8_t*)buf;
  while (n) {
    uint8_t k = min<uint8_t>(n, 8 - (dir % 8));
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// El ESP32-C3 tiene 2 canales RMT de salida: las 4 salidas se mandan una tras otra, abriendo el canal para cada una.
// La cantidad de LED, los segmentos ("letras") y el orden de color viven en la memoria del módulo (bytes 64-73):
// el letrero lleva su propia configuración.
const uint16_t PIX_MAX = 600;              // LED por salida
const uint8_t EEP_PIX = 64;
uint16_t pixN[4] = {0, 0, 0, 0};
uint8_t pixSeg = 0, pixOrden = 0;           // segmentos (0 = uno por salida); orden 0 GRB, 1 RGB, 2 BRG
uint16_t ablFactor = 1000;                  // limitación de brillo por corriente medida (0..1000)
// ---- módulo DMX: DMX512 por RS-485 (SP3485). DI = PWM1 (TX de UART1), RO = PWM2, DE = PWM3; /RE fijo en bajo,
// así el receptor regresa el eco de lo que se manda: con eso se reconoce el módulo. Dirección y canales: bytes 74-76.
const uint8_t EEP_DMX = 74;
uint16_t dmxDir = 1;                        // canal DMX del primer equipo (1-512)
uint8_t dmxCh = 3;                          // canales por equipo: 1 atenuador, 3 RGB, 4 RGBW
uint8_t dmxBuf[513];                        // [0] = código de inicio (0); [1..512] = canales
uint32_t dmxCuadros = 0;
void dmxAjustar() {                         // que todos los equipos quepan en el universo
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  if (unoDmx) {                                               // AP UNO: los 4 canales siguen; el RS-485 solo transmite
    rsDE(true);
    Serial1.setTxBufferSize(1024);
    Serial1.begin(250000, SERIAL_8N2, PIN_RS_RX, PIN_RS_TX);
    return;
  }
  if (modoDmx) {
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MbEscritura mbCola[4];
uint8_t mbEnCola = 0;
void rsDE(bool tx) {                                          // transmitir (1) o recibir (0)
  if (PIN_RS_DE != 255) { digitalWrite(PIN_RS_DE, tx); return; }
  unoDE = tx;                                                 // AP UNO: P7 del expansor 0x20 (las salidas S1-S4 no cambian)
  tcaEscribir(0x20, 1, (salEstado[0] & 0x0F) | (tx ? 0x80 : 0));
}
void mbIniciar() {
  const uint32_t CFG[4] = {SERIAL_8N1, SERIAL_8E1, SERIAL_8O1, SERIAL_8N2};
  if (PIN_RS_DE != 255) pinMode(PIN_RS_DE, OUTPUT);
  rsDE(false);                                                // recibir
  Serial1.begin(mbBaud, CFG[mbParidad & 3], PIN_RS_RX, PIN_RS_TX);
  Serial.printf("Modbus RTU: %lu baudios, paridad %u\n", (unsigned long)mbBaud, mbParidad);
}
bool mbPedirEscritura(uint8_t esclavo, uint8_t funcion, uint16_t reg, uint16_t valor) {
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  return s;
}

bool ordenDeGrupo(const char* o) {                       // por grupo solo viajan órdenes de luces
  return o[0] && o[0] != '@' && !strchr("WQKDZ!JFUY", o[0]) && strncmp(o, "MODELO", 6) && strncmp(o, "APRENDER", 8);
}

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  Wire.begin(PIN_SDA, PIN_SCL, 100000);
  modoUno = unoDetectar();
  if (modoUno) {                                             // AP UNO: RS-485 en IO1 (TX) e IO3 (RX), sin AUX ni IR
    PIN_RS_TX = 1; PIN_RS_RX = 3; PIN_RS_DE = 255;
    CC_PIN[0] = 0; CC_PIN[1] = 10;
    busModo = 0;                                             // sin CAN
    unoDmx = pref.getUChar("unodmx", 0) && !mbBaud;
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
